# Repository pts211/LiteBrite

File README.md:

# LiteBrite

LiteBrite is a project created for Cerner's DevCon 2019. Its original purpose was to be an interactive piece at the conference for spectators to play with. In throwing around ideas it was determined we could build something that would allow for more uses in the future. This LiteBrite is more of an interactive display. 

# Contributers
  - Paul Sites (paul.sites@cerner.com)
  - Aaron Kaplan (aaron.kaplan@cerner.com)
 
  The Lee's Summit North FIRST Robotics team, The Broncobots:
  - Joshua Wentworth
  - Chuck Stephenson
 
  Good friend
  - James Sietz
  
  Cerner Associates
  - Hans Perera
  - Max Phillips
  - Caitie Oder
  - ... and more!

# Features
- Animated erasing 
- Ripple effect
- Image Viewer
- Desktop display
- Save/Load Designs
- Usage Recorder
- Playback of timelapsed usage
- Screensaver/power save
- e1.31 support (TBD)
- Idle notifications (TBD)
- "Button Mash" mini-game (TBD)
- Clock (TBD)

# Design Details
LiteBrite features:
- 912 individually addressible RGB LED's
- 912 Arcade buttons
- 24 Arduino Nano's
- 24 Custom 40 input circuit boards
- 3 Adafruit FadeCandy boards
- Unmanaged network switch
- Interactivity handled through Processing.

# Usage Details
- DevCon: 111,314 presses (60,912; 50, 402)
- Maker Faire: 332,135 presses (188,901; 143,234)

Lifetime: 443,449 peg presses!

# Acknowledgements
Paul Sites and Aaron Kaplan designed, manufactured, and built LiteBrite but it was only possible with a lot of support, both from inside and outside of Cerner. 

Special thanks to Joshua Wentworth, for working tirelessly alongside us the entire step of the way.

... TODO .. Add it all up

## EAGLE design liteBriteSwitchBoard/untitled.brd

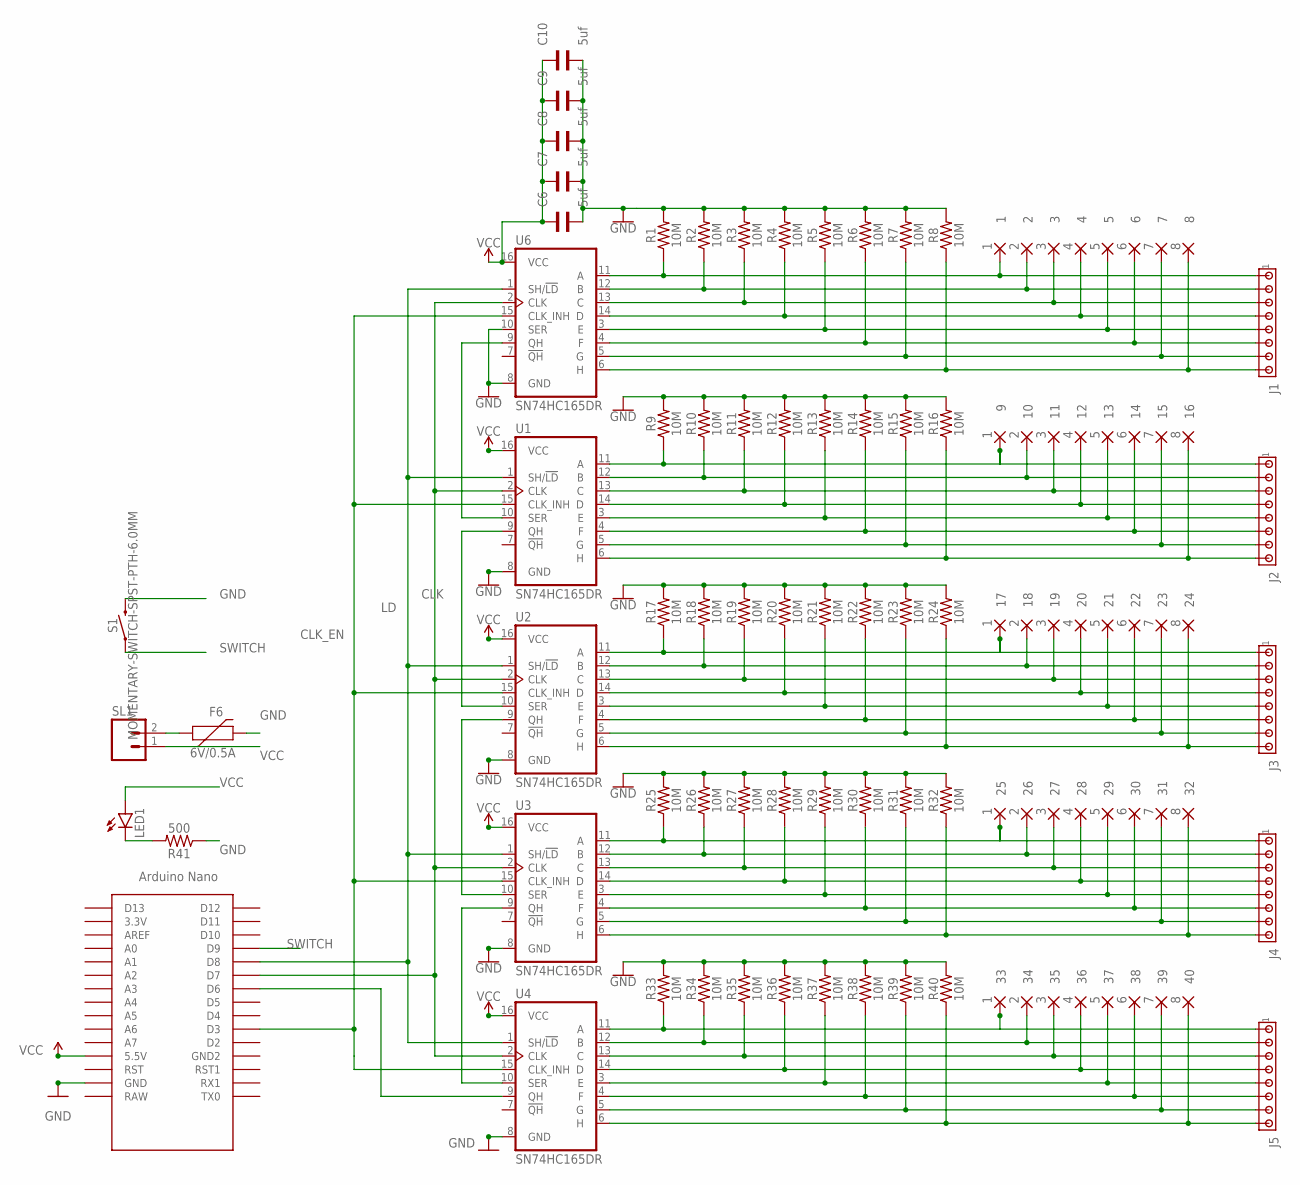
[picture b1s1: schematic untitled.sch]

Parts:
1, 9, 17, 25, 33: 1; 5-1,8
2, 10, 18, 26, 34: 2; 5-1,8
3, 11, 19, 27, 35: 3; 5-1,8
4, 12, 20, 28, 36: 4; 5-1,8
5, 13, 21, 29, 37: 5; 5-1,8
6, 14, 22, 30, 38: 6; 5-1,8
7, 15, 23, 31, 39: 7; 5-1,8
8, 16, 24, 32, 40: 8; 5-1,8
C6, C7, C8, C9, C10: 5uf; WCAP-CSGP_1206
F6: 6V/0.5A; 1206
J1, J2, J3, J4, J5: MTA08-100; 10X08MTA
LED1: LEDSML0805; SML0805
R1, R2, R3, R4, R5, R6, R7, R8, R9, R10, R11, R12, R13, R14, R15, R16, R17, R18, R19, R20, R21, R22, R23, R24, R25, R26, R27, R28, R29, R30, R31, R32, R33, R34, R35, R36, R37, R38, R39, R40: 10M; 0603
R41: 500; 0603
S1: MOMENTARY-SWITCH-SPST-PTH-6.0MM; TACTILE_SWITCH_PTH_6.0MM
SL1: M02; 02P
U1, U2, U3, U4, U6: SN74HC165DR; SO16
U$1: NANO

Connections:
B1: 2.1, J1.2, R2.1, U6.12 (B)
C1: 3.1, J1.3, R3.1, U6.13 (C)
CLK: U1.2 (CLK), U2.2 (CLK), U3.2 (CLK), U4.2 (CLK), U6.2 (CLK), U$1.D7
CLK_EN: U1.15 (CLK_INH), U2.15 (CLK_INH), U3.15 (CLK_INH), U4.15 (CLK_INH), U6.15 (CLK_INH), U$1.D3
D1: 4.1, J1.4, R4.1, U6.14 (D)
E1: 5.1, J1.5, R5.1, U6.3 (E)
F1: 6.1, J1.6, R6.1, U6.4 (F)
G1: 7.1, J1.7, R7.1, U6.5 (G)
GND: C6.1, C7.1, C8.1, C9.1, C10.1, F6.2, R1.2, R2.2, R3.2, R4.2, R5.2, R6.2, R7.2, R8.2, R9.2, R10.2, R11.2, R12.2, R13.2, R14.2, R15.2, R16.2, R17.2, R18.2, R19.2, R20.2, R21.2, R22.2, R23.2, R24.2, R25.2, R26.2, R27.2, R28.2, R29.2, R30.2, R31.2, R32.2, R33.2, R34.2, R35.2, R36.2, R37.2, R38.2, R39.2, R40.2, R41.1, S1.3 (2), U1.8 (GND), U2.8 (GND), U3.8 (GND), U4.8 (GND), U6.8 (GND), U6.10 (SER), U$1.GND
H1: 8.1, J1.8, R8.1, U6.6 (H)
LD: U1.1 (SH/!LD), U2.1 (SH/!LD), U3.1 (SH/!LD), U4.1 (SH/!LD), U6.1 (SH/!LD), U$1.D8
unnamed: U1.10 (SER), U6.9 (QH)
unnamed: U1.9 (QH), U2.10 (SER)
unnamed: U2.9 (QH), U3.10 (SER)
unnamed: U3.9 (QH), U4.10 (SER)
unnamed: 1.1, J1.1, R1.1, U6.11 (A)
unnamed: F6.1, SL1.2
unnamed: U4.9 (QH), U$1.D6
unnamed: LED1.C, R41.2
unnamed: 9.1, J2.1, R9.1, U1.11 (A)
unnamed: 10.1, J2.2, R10.1, U1.12 (B)
unnamed: 11.1, J2.3, R11.1, U1.13 (C)
unnamed: 12.1, J2.4, R12.1, U1.14 (D)
unnamed: 13.1, J2.5, R13.1, U1.3 (E)
unnamed: 14.1, J2.6, R14.1, U1.4 (F)
unnamed: 15.1, J2.7, R15.1, U1.5 (G)
unnamed: 16.1, J2.8, R16.1, U1.6 (H)
unnamed: 17.1, J3.1, R17.1, U2.11 (A)
unnamed: 18.1, J3.2, R18.1, U2.12 (B)
unnamed: 19.1, J3.3, R19.1, U2.13 (C)
unnamed: 20.1, J3.4, R20.1, U2.14 (D)
unnamed: 21.1, J3.5, R21.1, U2.3 (E)
unnamed: 22.1, J3.6, R22.1, U2.4 (F)
unnamed: 23.1, J3.7, R23.1, U2.5 (G)
unnamed: 24.1, J3.8, R24.1, U2.6 (H)
unnamed: 25.1, J4.1, R25.1, U3.11 (A)
unnamed: 26.1, J4.2, R26.1, U3.12 (B)
unnamed: 27.1, J4.3, R27.1, U3.13 (C)
unnamed: 28.1, J4.4, R28.1, U3.14 (D)
unnamed: 29.1, J4.5, R29.1, U3.3 (E)
unnamed: 30.1, J4.6, R30.1, U3.4 (F)
unnamed: 31.1, J4.7, R31.1, U3.5 (G)
unnamed: 32.1, J4.8, R32.1, U3.6 (H)
unnamed: 33.1, J5.1, R33.1, U4.11 (A)
unnamed: 34.1, J5.2, R34.1, U4.12 (B)
unnamed: 35.1, J5.3, R35.1, U4.13 (C)
unnamed: 36.1, J5.4, R36.1, U4.14 (D)
unnamed: 37.1, J5.5, R37.1, U4.3 (E)
unnamed: 38.1, J5.6, R38.1, U4.4 (F)
unnamed: 39.1, J5.7, R39.1, U4.5 (G)
unnamed: 40.1, J5.8, R40.1, U4.6 (H)
SWITCH: S1.1, U$1.D9
VCC: C6.2, C7.2, C8.2, C9.2, C10.2, LED1.A, SL1.1, U1.16 (VCC), U2.16 (VCC), U3.16 (VCC), U4.16 (VCC), U6.16 (VCC), U$1.5V (5.5V)

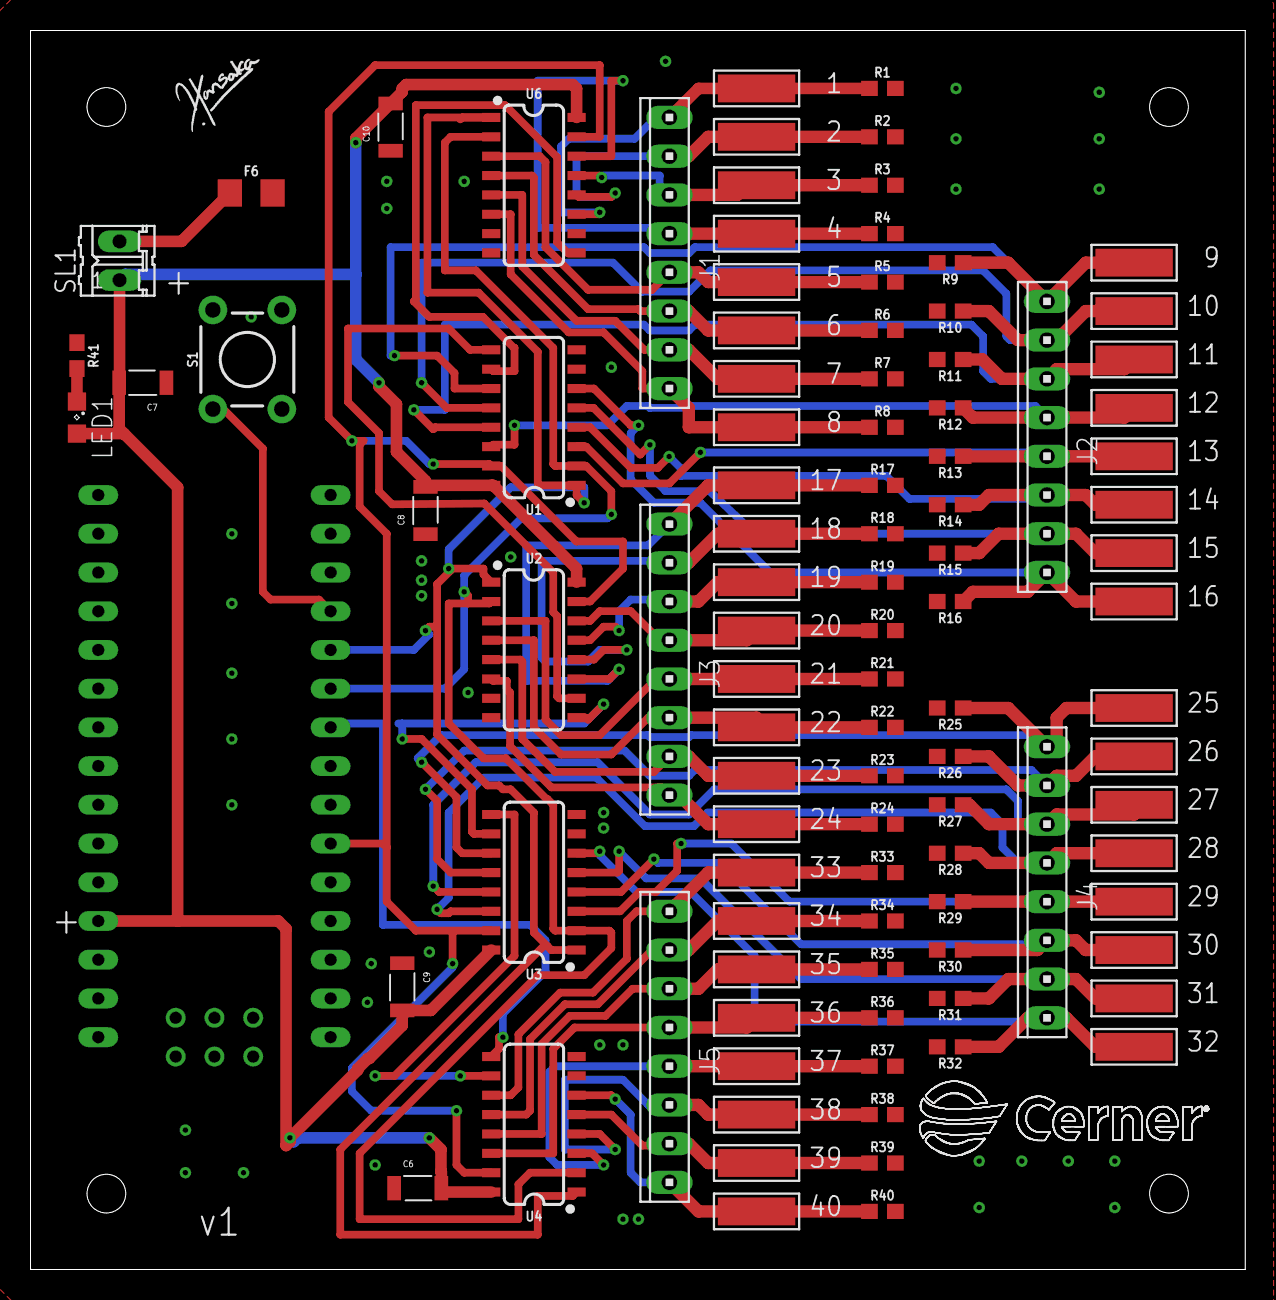
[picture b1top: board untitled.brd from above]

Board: 2 copper layers, 79.7 x 81.3 mm, 107 parts (0 on the bottom side), 53 nets.

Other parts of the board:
U$2, U$3, U$4, U$5: DRILL_0.1000
U$6: SIGNATURE
U$7: CERNER

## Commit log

2019-05-05 hardened containment check, removed magic numbers.
2019-05-06 networking IP
2019-05-06 Moved grid operations to dedicated class.
2019-05-07 Made it easy to toggle staggered.
2019-05-07 Added image view - quick and dirty. Will be cleaned up later.
2019-05-08 Now an image can be "modified" after it is shown by clicking pegs.
2019-05-11 comitting latest
2019-05-14 Updated ButtonNode to handle sending buttons over network.
2019-05-14 Tidying up ButtonNode
2019-05-14 Updated logic to only send changes of button state to pressed.
2019-05-14 FIXED THE UDP PROBLEM!!! Turns out UDP consumers typically like the destination MAC address populated. Wouldn't you know it, the EtherCard library doesn't send the desination MAC in a lot of scenario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
2019-05-14 Updated ButtonNode for easy mass deployment. Added documentation.
2019-05-14 More documentation. Updated UDP message processing.
2019-05-15 Added initial animated clear.
2019-05-17 Lots of general updates. Created test for ripple.
2019-05-17 Added an optional, but fun, ripple effect.
2019-05-20 General updates
2019-05-20 Updated to use Processing 3.
2019-05-20 Started created GUI for settings with G4P.
2019-05-20 Added live desktop viewer.
2019-05-22 v1 board
2019-05-29 General updates. Started on README.
2019-05-29 Spelling.
2019-05-30 Feature additions! Added startup sequence. Added rainbow. Added random.
2019-05-30 Updated intro.
2019-05-31 Fixed corrupted G4P configuration.
2019-05-31 Added design history tracking
2019-05-31 Added color slider. Need to implement.
2019-05-31 Custom color slider functionality.
2019-06-01 Updated pixel mapping.
2019-06-01 Fixed button logic.
2019-06-02 Updated button logic data types. Can now read from all the buttons!
2019-06-04 Initial button calibration working. Still need to save to EEPROM.
2019-06-04 Finished Arduino Software. General updates.
2019-06-05 add better cern logo and missing dev tool zip.
2019-06-05 SEND IT.
2019-06-07 Made it through DevCon!
2019-06-10 Updated with screensaver and corrected CSV file writing.
2019-06-10 Few tweaks before leaving it in the lobby.
2019-06-11 Lots of updates. Improved recording that will split up files on clear. Started on playback. General clean up.
2019-06-12 Added walk by timeout. Updated timer logic. Updated logging.
2019-06-20 Updating wtih latest timelapse data and LiteBrite settings
2019-06-20 Updated to only write one clear message.
2019-06-20 Adding playback controls for recorded files with directory scanning.
2019-06-20 Added designs so far.
2019-06-20 Updated playback to persist at the end.
2019-06-21 Playback screensaver. Added Initial color feature.
2019-06-22 Updated recordings .7z
2019-06-23 Adding maker faire day 01 data. Fixed ripple.
2019-06-24 Adding Maker Faire Day 02 data.
2019-06-24 Removed one of the test projects. Updated readme. Updated data archive.
2019-06-24 Updated timeouts before sleeping.
2019-07-01 Adding last weeks recordings. Corrected issue with folder naming.
2019-07-02 Updated favorites to include week of 6/23
2019-07-02 Added 7/01 favorite
2019-09-18 Adding latest recordings

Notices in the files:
parts and their libraries:
Wurth_Elektronik_Passive_Capacitors_rev1: Copyright: Würth Elektronik
SparkFun-Resistors: Licensing: Creative Commons ShareAlike 4.0 International - https://creativecommons.org/licenses/by-sa/4.0
